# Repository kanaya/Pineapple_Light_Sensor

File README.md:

Pineapple_Light_Sensor
======================

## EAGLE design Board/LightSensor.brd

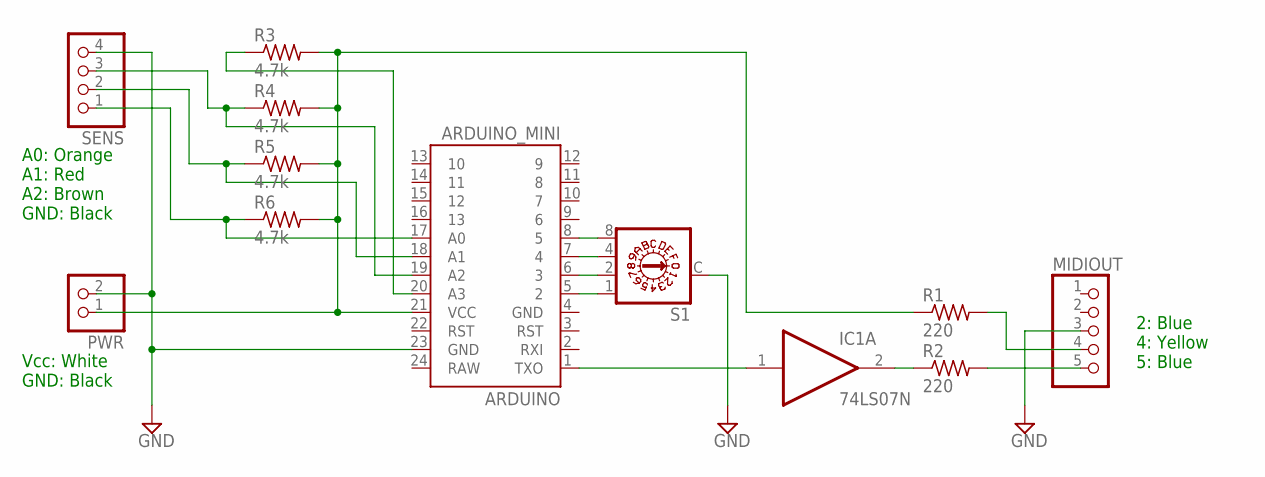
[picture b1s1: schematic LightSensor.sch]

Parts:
ARDUINO: ARDUINO_MINI
IC1: 74LS07N; DIL14
MIDIOUT: PINHD-1X5; 1X05
PWR: PINHD-1X2; 1X02
R1, R2: 220; 0204/5
R3, R4, R5, R6: 4.7k; 0204/5
S1: A1353HEX
SENS: PINHD-1X4; 1X04

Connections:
GND: ARDUINO.23 (GND), IC1.7 (GND), MIDIOUT.3, PWR.2, S1.C, SENS.4
unnamed: ARDUINO.1 (TXO), IC1.1 (I)
unnamed: IC1.2 (O), R2.1
unnamed: ARDUINO.21 (VCC), PWR.1, R1.1, R3.2, R4.2, R5.2, R6.2
unnamed: MIDIOUT.5, R2.2
unnamed: MIDIOUT.4, R1.2
unnamed: ARDUINO.20 (A3), R3.1
unnamed: ARDUINO.19 (A2), R4.1, SENS.3
unnamed: ARDUINO.18 (A1), R5.1, SENS.2
unnamed: ARDUINO.17 (A0), R6.1, SENS.1
unnamed: ARDUINO.5 (2), S1.1
unnamed: ARDUINO.6 (3), S1.2
unnamed: ARDUINO.7 (4), S1.4
unnamed: ARDUINO.8 (5), S1.8
VCC: IC1.14 (VCC)

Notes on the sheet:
A0: Orange A1: Red A2: Brown GND: Black
Vcc: White GND: Black
2: Blue 4: Yellow 5: Blue

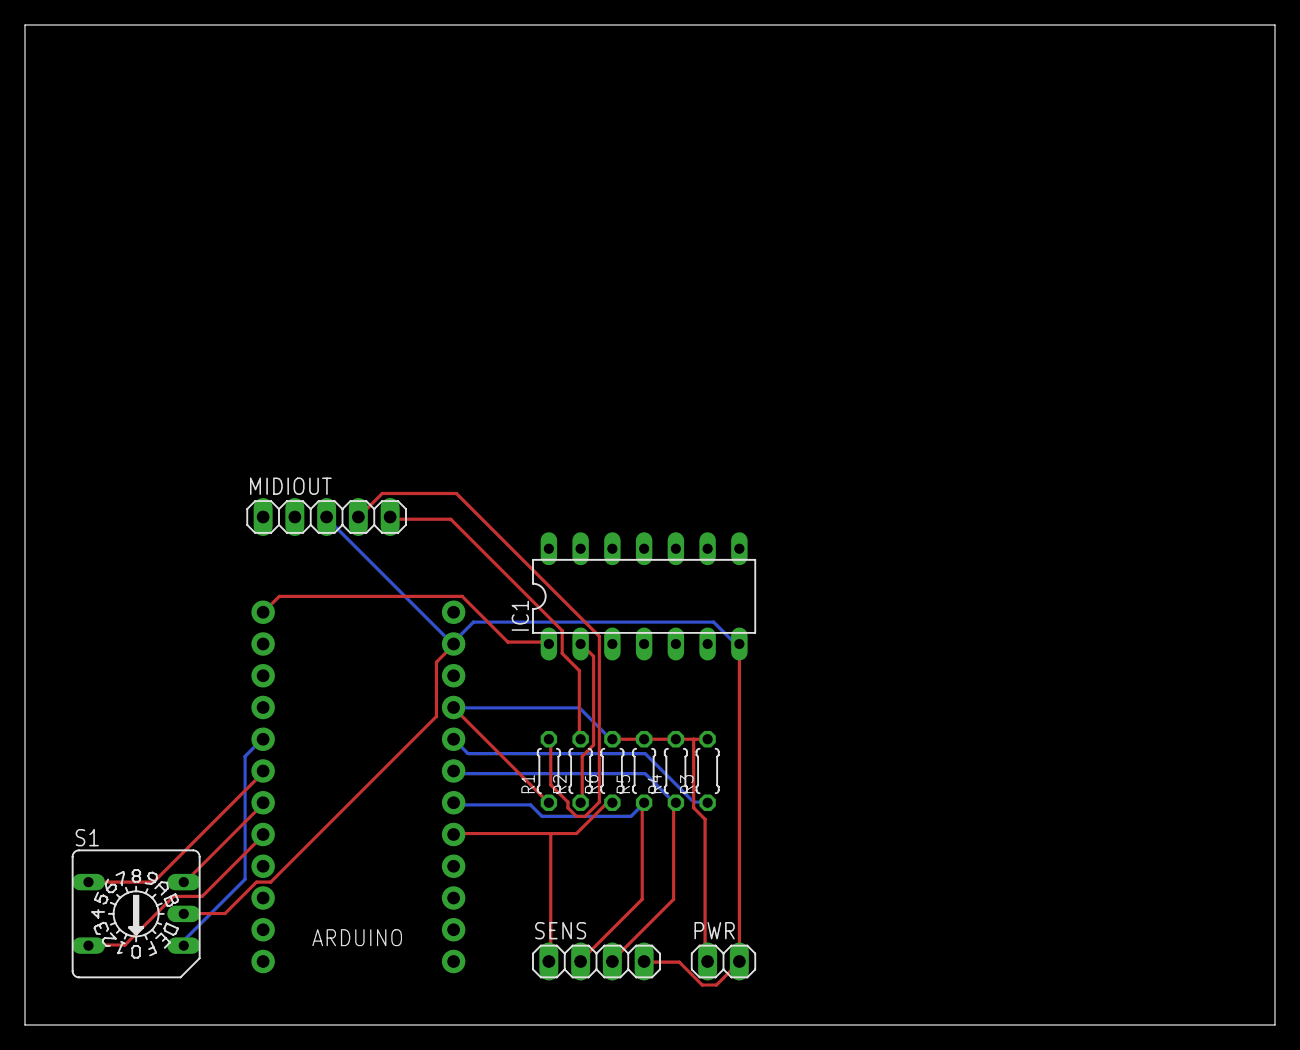
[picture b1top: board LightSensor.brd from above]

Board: 2 copper layers, 100.0 x 80.0 mm, 12 parts (0 on the bottom side), 14 nets.

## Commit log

2014-12-08 Initial commit.
2014-12-19 Num of sensors from 4 to 3.
2014-12-19 Rotary sw.
2014-12-19 Added LightSensor2. Use LightSensor2, not LightSensor.
2014-12-19 Refined.

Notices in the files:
parts and their libraries:
SparkFun-Boards: Licensing: Creative Commons ShareAlike 4.0 International - https://creativecommons.org/licenses/by-sa/4.0
